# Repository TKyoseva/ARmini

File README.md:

# parts-bot

Written by `.github/workflows/parts.yml`. Do not edit; edit `parts/needs.yaml` on `dev`.

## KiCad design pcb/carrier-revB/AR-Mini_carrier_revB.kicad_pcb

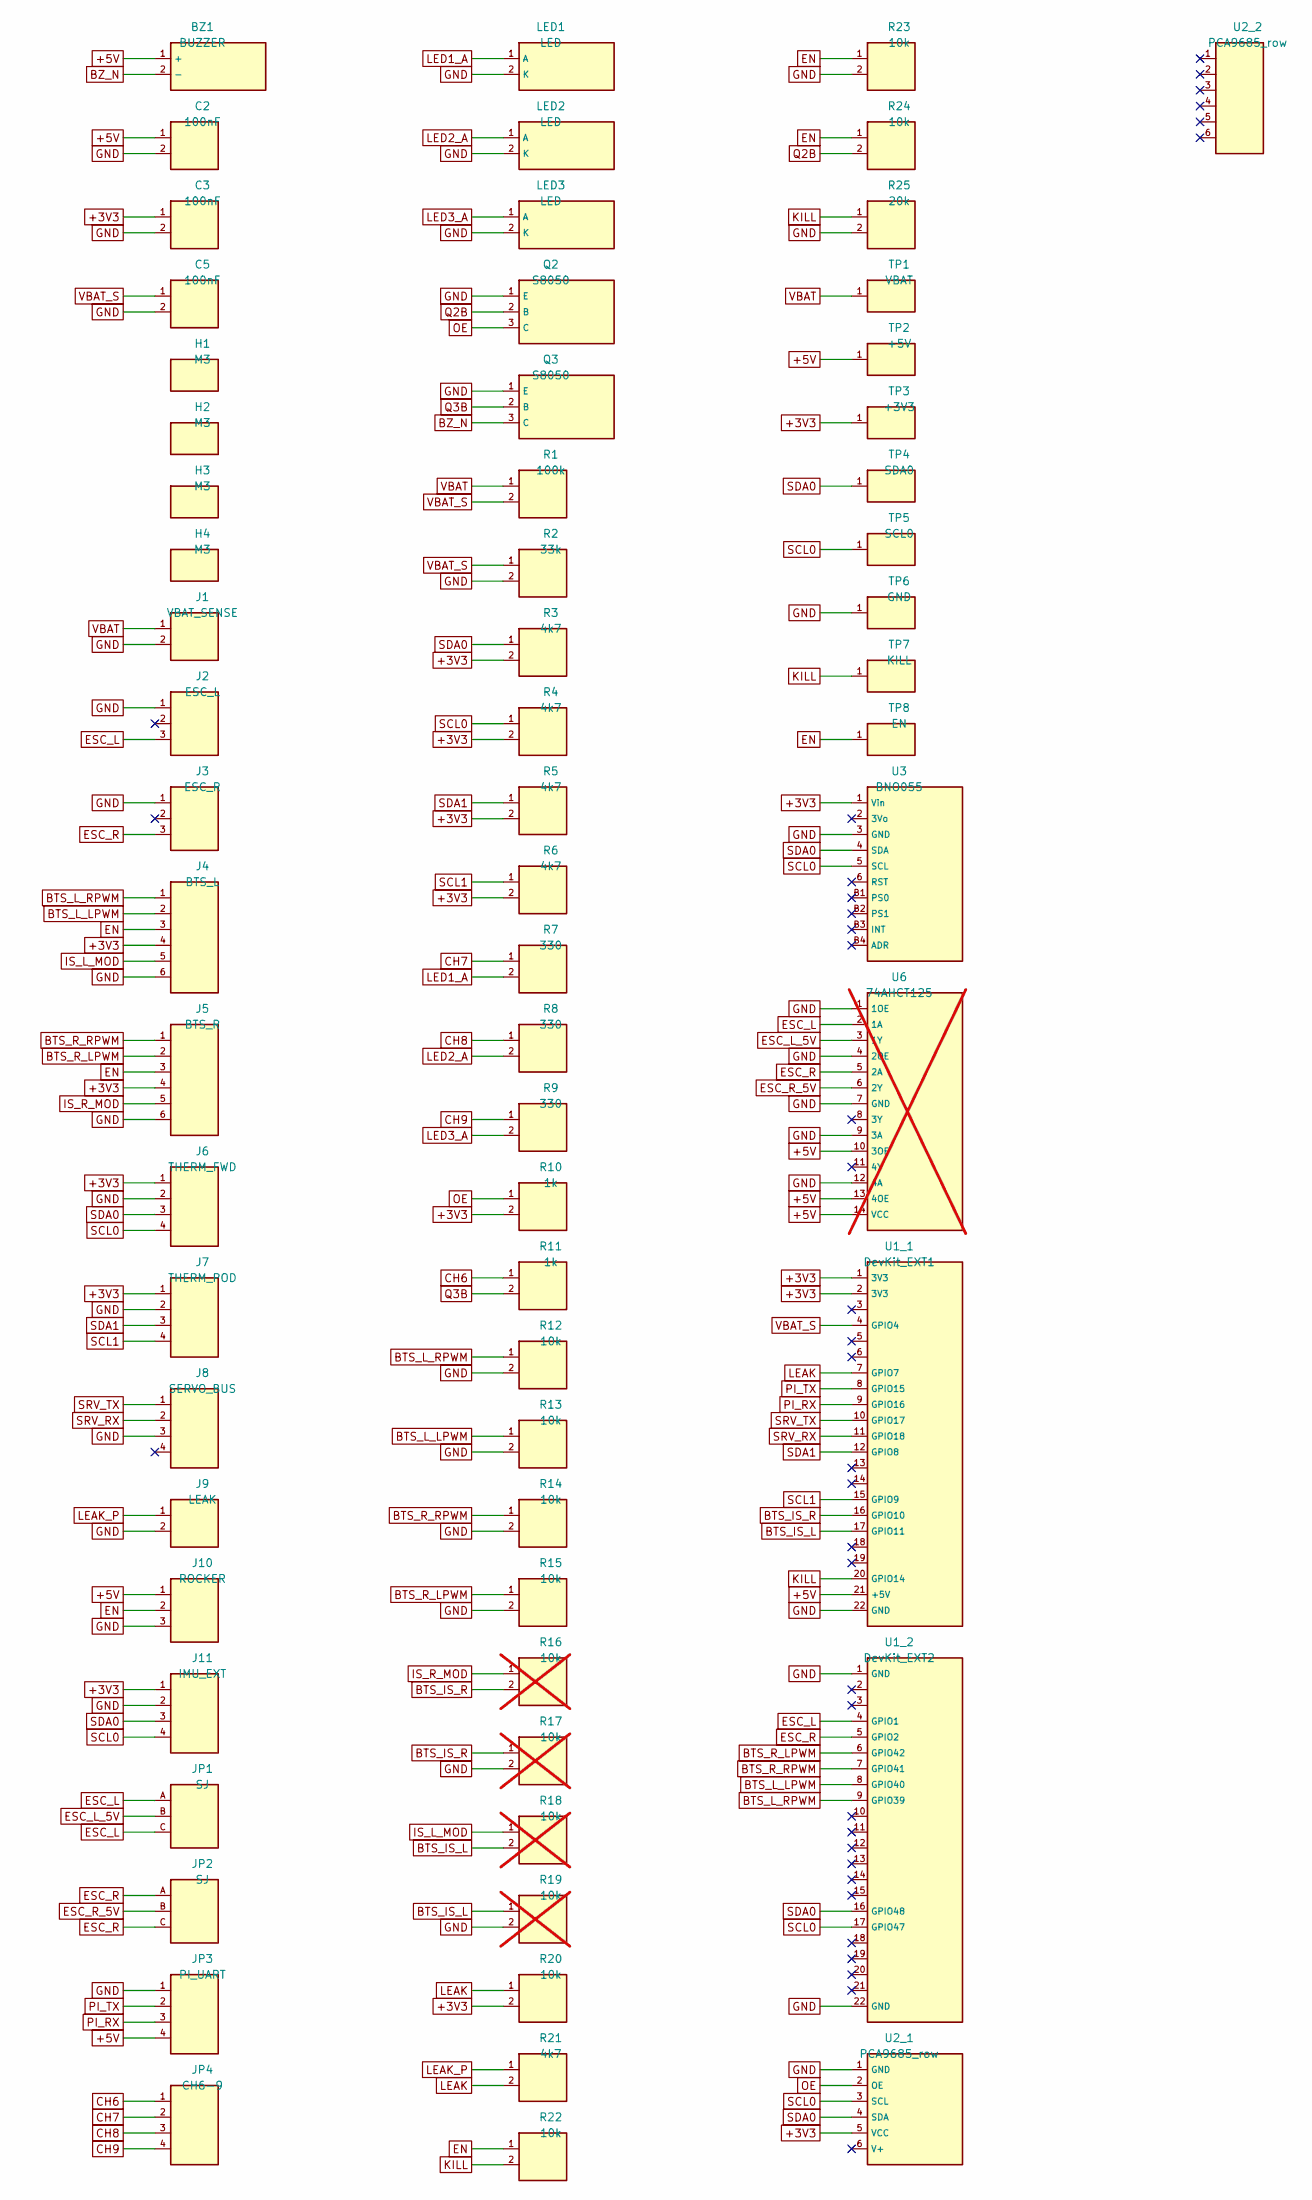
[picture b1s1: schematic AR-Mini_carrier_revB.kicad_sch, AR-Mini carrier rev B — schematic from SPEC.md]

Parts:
BZ1: BUZZER; BZ1
C2: 100nF; C2
C3: 100nF; C3
C5: 100nF; C5
H1, H2, H3, H4: M3
J1: VBAT_SENSE; J1
J2: ESC_L; J2
J3: ESC_R; J3
J4: BTS_L; J4
J5: BTS_R; J5
J6: THERM_FWD; J6
J7: THERM_POD; J7
J8: SERVO_BUS; J8
J9: LEAK; J9
J10: ROCKER; J10
J11: IMU_EXT; J11
JP1: SJ; JP1
JP2: SJ; JP2
JP3: PI_UART; JP3
JP4: CH6-9; JP4
LED1: LED; LED1
LED2: LED; LED2
LED3: LED; LED3
Q2: S8050; Q2
Q3: S8050; Q3
R1: 100k; R1
R2: 33k; R2
R3: 4k7; R3
R4: 4k7; R4
R5: 4k7; R5
R6: 4k7; R6
R7: 330; R7
R8: 330; R8
R9: 330; R9
R10: 1k; R10
R11: 1k; R11
R12: 10k; R12
R13: 10k; R13
R14: 10k; R14
R15: 10k; R15
R16: 10k; R16; not fitted
R17: 10k; R17; not fitted
R18: 10k; R18; not fitted
R19: 10k; R19; not fitted
R20: 10k; R20
R21: 4k7; R21
R22: 10k; R22
R23: 10k; R23
R24: 10k; R24
R25: 20k; R25
TP1: VBAT; TP1
TP2: +5V; TP2
TP3: +3V3; TP3
TP4: SDA0; TP4
TP5: SCL0; TP5
TP6: GND; TP6
TP7: KILL; TP7
TP8: EN; TP8
U1_1: DevKit_EXT1; U1_1
U1_2: DevKit_EXT2; U1_2
U2_1: PCA9685_row; U2_1
U2_2: PCA9685_row; U2_2
U3: BNO055; U3
U6: 74AHCT125; U6; not fitted

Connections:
+3V3: C3.1, J4.4, J5.4, J6.1, J7.1, J11.1, R3.2, R4.2, R5.2, R6.2, R10.2, R20.2, TP3.1, U1_1.1 (3V3), U1_1.2 (3V3), U2_1.5 (VCC), U3.1 (Vin)
+5V: BZ1.1 (+), C2.1, J10.1, JP3.4, TP2.1, U1_1.21 (+5V), U6.10 (3OE), U6.13 (4OE), U6.14 (VCC)
BTS_IS_L: R18.2, R19.1, U1_1.17 (GPIO11)
BTS_IS_R: R16.2, R17.1, U1_1.16 (GPIO10)
BTS_L_LPWM: J4.2, R13.1, U1_2.8 (GPIO40)
BTS_L_RPWM: J4.1, R12.1, U1_2.9 (GPIO39)
BTS_R_LPWM: J5.2, R15.1, U1_2.6 (GPIO42)
BTS_R_RPWM: J5.1, R14.1, U1_2.7 (GPIO41)
BZ_N: BZ1.2 (-), Q3.3 (C)
CH6: JP4.1, R11.1
CH7: JP4.2, R7.1
CH8: JP4.3, R8.1
CH9: JP4.4, R9.1
EN: J4.3, J5.3, J10.2, R22.1, R23.1, R24.1, TP8.1
ESC_L: J2.3, JP1.A, JP1.C, U1_2.4 (GPIO1), U6.2 (1A)
ESC_L_5V: JP1.B, U6.3 (1Y)
ESC_R: J3.3, JP2.A, JP2.C, U1_2.5 (GPIO2), U6.5 (2A)
ESC_R_5V: JP2.B, U6.6 (2Y)
GND: C2.2, C3.2, C5.2, J1.2, J2.1, J3.1, J4.6, J5.6, J6.2, J7.2, J8.3, J9.2, J10.3, J11.2, JP3.1, LED1.2 (K), LED2.2 (K), LED3.2 (K), Q2.1 (E), Q3.1 (E), R2.2, R12.2, R13.2, R14.2, R15.2, R17.2, R19.2, R23.2, R25.2, TP6.1, U1_1.22 (GND), U1_2.1 (GND), U1_2.22 (GND), U2_1.1 (GND), U3.3 (GND), U6.1 (1OE), U6.4 (2OE), U6.7 (GND), U6.9 (3A), U6.12 (4A)
IS_L_MOD: J4.5, R18.1
IS_R_MOD: J5.5, R16.1
KILL: R22.2, R25.1, TP7.1, U1_1.20 (GPIO14)
LEAK: R20.1, R21.2, U1_1.7 (GPIO7)
LEAK_P: J9.1, R21.1
LED1_A: LED1.1 (A), R7.2
LED2_A: LED2.1 (A), R8.2
LED3_A: LED3.1 (A), R9.2
OE: Q2.3 (C), R10.1, U2_1.2 (OE)
PI_RX: JP3.3, U1_1.9 (GPIO16)
PI_TX: JP3.2, U1_1.8 (GPIO15)
Q2B: Q2.2 (B), R24.2
Q3B: Q3.2 (B), R11.2
SCL0: J6.4, J11.4, R4.1, TP5.1, U1_2.17 (GPIO47), U2_1.3 (SCL), U3.5 (SCL)
SCL1: J7.4, R6.1, U1_1.15 (GPIO9)
SDA0: J6.3, J11.3, R3.1, TP4.1, U1_2.16 (GPIO48), U2_1.4 (SDA), U3.4 (SDA)
SDA1: J7.3, R5.1, U1_1.12 (GPIO8)
SRV_RX: J8.2, U1_1.11 (GPIO18)
SRV_TX: J8.1, U1_1.10 (GPIO17)
VBAT: J1.1, R1.1, TP1.1
VBAT_S: C5.1, R1.2, R2.1, U1_1.4 (GPIO4)

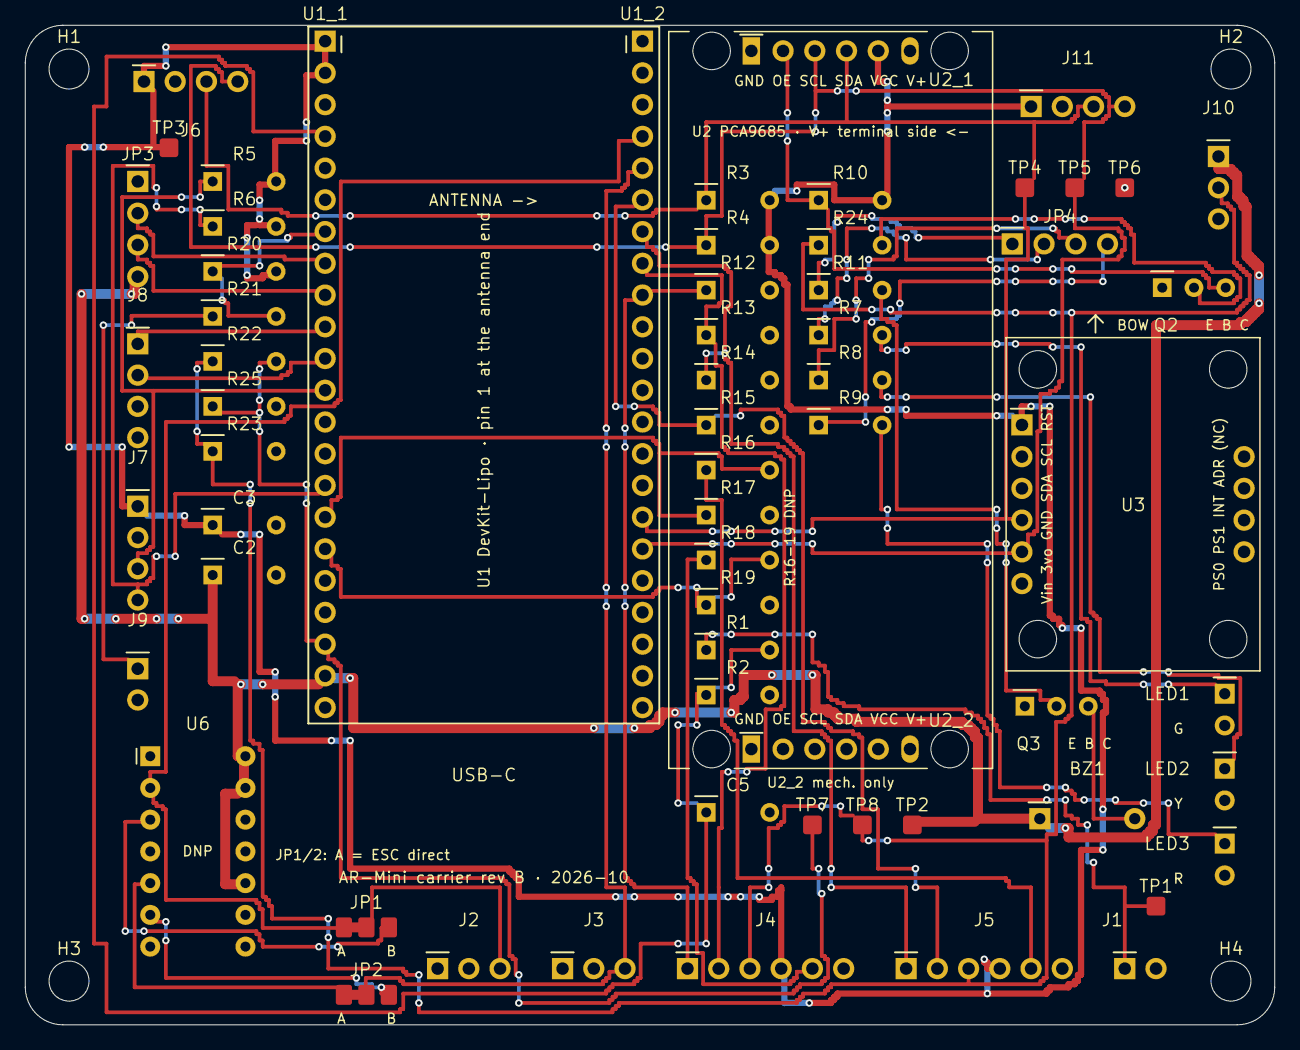
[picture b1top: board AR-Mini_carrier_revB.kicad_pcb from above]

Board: 2 copper layers, 100.0 x 80.0 mm, 67 parts (0 on the bottom side), 40 nets.

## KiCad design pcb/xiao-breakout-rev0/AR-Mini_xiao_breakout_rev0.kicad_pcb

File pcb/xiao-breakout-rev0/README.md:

# AR-Mini XIAO breakout — rev 0 (learning board for Aisler)

50 × 40 mm, 2 layers, THT only. Goal: go the whole way KiCad → DRC → Aisler → soldering → it works, with something that is really used afterwards: this is the XIAO part of the carrier board (sensors, servo bus, 5 V input, battery).

## What is on it
- J1/J2 — 2 × 1×7 female headers for the XIAO ESP32S3 Sense (15.24 mm between the rows). The XIAO's USB-C faces the top edge (silkscreen "USB-C ^").
- J3 I2C0 (JST-XH 4): 3V3 · GND · SDA0 (D4/GPIO5) · SCL0 (D5/GPIO6) → MLX90642-D45, BNO055, PCA9685
- J4 I2C1 (JST-XH 4): **SCL1 (D2/GPIO3) · SDA1 (D3/GPIO4)** · GND · 3V3 → MLX90640-110°. The pin order differs from J3 — on purpose, see the note.
- J5 SERVO (JST-XH 4): RX (D7/GPIO44 ← driver TX) · TX (D6/GPIO43 → driver RX) · GND · NC
- J6 PWR (JST-XH 2): +5 V · GND — from the buck
- J7 VBAT (JST-XH 2): VBAT · GND — from the "5 A logic" fuse (measurement only, almost zero current)
- R1 100k / R2 33k — divider to A0 (D0/GPIO1): 12.6 V → 3.13 V
- R7 330 Ω + LED1 — 3V3 indicator (on = the XIAO is alive)
- H1–H4 — Ø3.2 mounting holes, grid 44 × 34
- GND — pour on the bottom layer; 3V3 and I2C-1 are routed on the bottom, everything else on top.

Note: `Wire1.begin(4, 3)` (SDA=GPIO4, SCL=GPIO3). They are swapped so the tracks do not cross; the carrier board is the same.

## How to open and check it (10 minutes)
1. KiCad 8 or 9 → **PCB Editor** (standalone, without a project) → File → Open → `AR-Mini_xiao_breakout_rev0.kicad_pcb`. The file is in KiCad 7 format; on Save it will be converted — that is normal.
2. Press **B** (Fill all zones) — the bottom layer fills with ground.
3. **Inspect → Design Rules Checker → Run DRC.** Expect 0 errors. Warnings like "footprint not found in library" / "no schematic" are normal for a standalone board — ignore them.
4. **View → 3D Viewer** (Alt+3) — look at it. The headers and JSTs will have no 3D models (generated footprints), only pads — that is fine.
5. To change it before ordering: move tracks with **M**, add them with **X**; Edit → Edit Text and Graphics for the labels.

## Ordering from Aisler (5 minutes)
- Simplest: **aisler.net → New project → Upload** → upload the `.kicad_pcb` directly (they accept KiCad files; no Gerbers needed).
- Or: Plugin and Content Manager → install "AISLER Push for KiCad" → toolbar button → opens the site with the board uploaded.
- Choose: 2 Layer · 1.6 mm · **3 pcs** (minimum) · lead-free HASL (or "Beautiful Boards" for a black mask, +~10 €) · delivery to Bulgaria.
- Expected price: ~15–20 € for three. Lead time: 3–5 working days production + DHL.
- Before "Order": print 1:1 on paper (File → Plot → PDF, scale 1:1) and put the XIAO and the JSTs on the sheet. Every pin in its hole.

## Parts to solder (all THT, 15 minutes with the HS-03)
| What | Qty | From |
|---|---|---|
| Female header 1×7, 2.54 | 2 | Freenove/Joy-IT kit or Ardboard |
| JST-XH 2.5 mm vertical PCB header, 4 pins | 3 | Vikiwat / Ardboard (~0.20 €) |
| JST-XH vertical, 2 pins | 2 | same |
| Resistors 100k, 33k, 330 Ω (1/4 W) | 1 each | the Freenove kit has 330; 100k/33k from Vikiwat |
| LED 5 mm | 1 | the kit |
| M3 × 6 mm standoffs + screws | 4 | ruthex / DSM set |

Soldering order: resistors → LED → JSTs → headers last (with the XIAO plugged in, so they stay parallel).

## What it teaches that goes into the carrier rev A
- whether the 15.24 mm headers fit this XIAO (measured 15.35);
- whether JST-XH pads with a Ø1.0 hole are comfortable for the crimped wires from the Preciva kit;
- how accurate a 1:1 print is on the paper printer;
- how long it really takes from "Order" to "on the desk" with Aisler for Bulgaria — that number is needed for the rev A schedule.

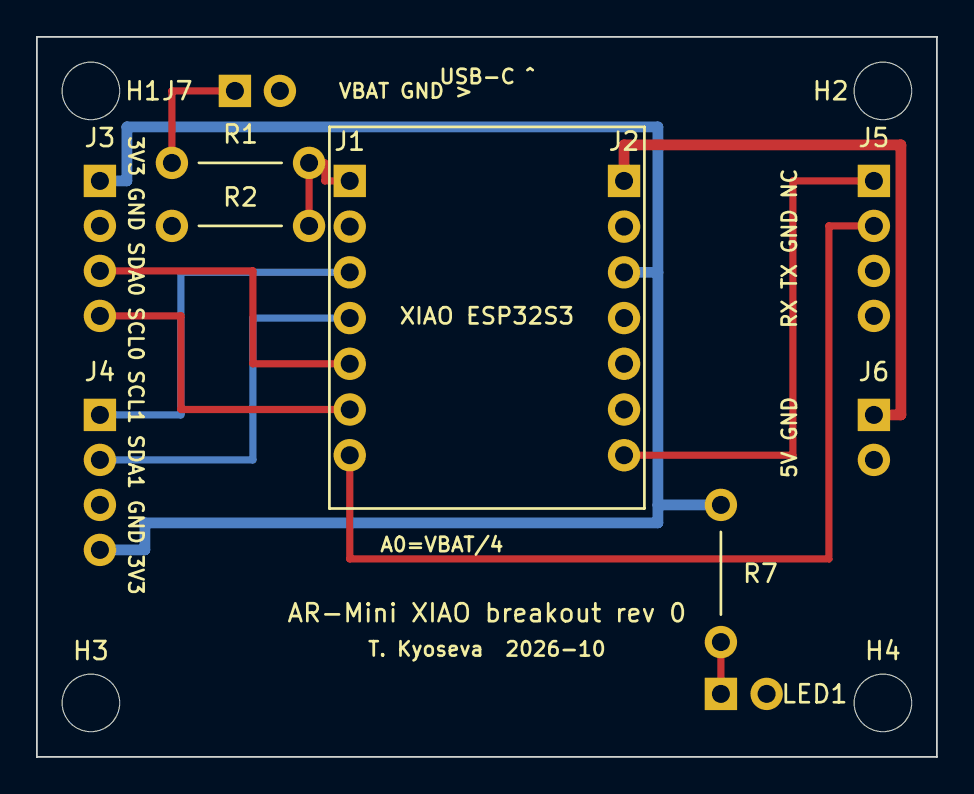
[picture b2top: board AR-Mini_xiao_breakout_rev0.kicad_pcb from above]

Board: 2 copper layers, 50.0 x 40.0 mm, 15 parts (0 on the bottom side), 12 nets.

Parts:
H1, H2, H3, H4: M3
J1: XIAO_L
J2: XIAO_R
J3: I2C0
J4: I2C1
J5: SERVO
J6: PWR5V
J7: VBAT
LED1: PWR
R1: 100k
R2: 33k
R7: 330

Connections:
+3V3: J2.3, J3.1, J4.4, R7.1
+5V: J2.1, J6.1
GND: J2.2, J3.2, J4.3, J5.3, J6.2, J7.2, LED1.2, R2.1
LED_A: LED1.1, R7.2
SCL0: J1.6, J3.4
SCL1: J1.3, J4.1
SDA0: J1.5, J3.3
SDA1: J1.4, J4.2
SRV_RX: J2.7, J5.1
SRV_TX: J1.7, J5.2
VBAT: J7.1, R1.1
VBAT_S: J1.1, R1.2, R2.2

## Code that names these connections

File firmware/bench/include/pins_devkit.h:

// AR-Mini bench · Olimex ESP32-S3-DevKit-Lipo · the ONE place for GPIO numbers.
//
// SOURCE: hardware/breadboard/AR-Mini_breadboard_2b_devkit-lipo.png, table "AR-Mini pins on the DevKit-Lipo"
//         (sheet 2b, T. Kyoseva, 07.10.2026) and hardware/breadboard/Olimex_DevKit-Lipo_pinout_manual-p7.png
//         (Olimex ESP32-S3-DevKit-Lipo user manual rev 2.0, p7, EXT1/EXT2 = DevKitC-1 compatible).
// Every `// VERIFY` below is also listed at the bottom of hardware/wiring/PINOUT.md and in firmware/bench/README.md.
#pragma once

// ---------------------------------------------------------------- I2C-0 (Wire): D45, BNO055, PCA9685 (= pUEXT pins)
#define PIN_I2C0_SDA 48 // SOURCE: breadboard 2b (I²C-0 SDA GPIO48; also pUEXT / manual p7 "GPIO48\I2C_SDA")
#define PIN_I2C0_SCL 47 // SOURCE: breadboard 2b (I²C-0 SCL GPIO47; also pUEXT / manual p7 "GPIO47\I2C_SCL")

// ---------------------------------------------------------------- I2C-1 (Wire1): MLX90640 110°
#define PIN_I2C1_SDA 8 // SOURCE: breadboard 2b (I²C-1 SDA GPIO8, EXT1 row a)
#define PIN_I2C1_SCL 9 // SOURCE: breadboard 2b (I²C-1 SCL GPIO9, EXT1 row a)

// ---------------------------------------------------------------- UART1: Waveshare bus servo adapter
#define PIN_SRV_TX 17 // SOURCE: breadboard 2b (UART1 TX GPIO17 = U1TXD → adapter RX)
#define PIN_SRV_RX 18 // SOURCE: breadboard 2b (UART1 RX GPIO18 = U1RXD ← adapter TX)

// ---------------------------------------------------------------- UART2 (v2): Raspberry Pi 5 — not used on the bench
#define PIN_PI_TX 15 // SOURCE: breadboard 2b (UART2 TX GPIO15)
#define PIN_PI_RX 16 // SOURCE: breadboard 2b (UART2 RX GPIO16)

// ---------------------------------------------------------------- ESC L / R (LEDC 50 Hz) — bench env `esc` (C024)
#define PIN_ESC_L 1 // SOURCE: breadboard 2b (ESC L GPIO1)
#define PIN_ESC_R 2 // SOURCE: breadboard 2b (ESC R GPIO2)

// ---------------------------------------------------------------- BTS7960 L / R
// Sheet 2b gives the pairs "GPIO39/40 · GPIO41/42" but not which one of a pair is RPWM.
// Chosen here: the lower number is RPWM. If the motor runs the wrong way, swap the two wires, not the code.
// GPIO39-42 each have a 10 k pull-down to GND (C015, 11.10): GPIO39 is weakly HIGH after boot and 39/40 in download mode.
// setup() must drive all four LOW before anything else. The rocker (R_EN/L_EN) stays the hardware stop.
#define PIN_BTS_L_RPWM 39 // VERIFY: sheet 2b "BTS7960 L GPIO39/40" — RPWM/LPWM order chosen, not on the sheet
#define PIN_BTS_L_LPWM 40 // VERIFY: see PIN_BTS_L_RPWM
#define PIN_BTS_R_RPWM 41 // VERIFY: sheet 2b "BTS7960 R GPIO41/42" — order chosen, not on the sheet
#define PIN_BTS_R_LPWM 42 // VERIFY: see PIN_BTS_R_RPWM
// BTS7960 current sense (IS_R, IS_L) is NOT on sheet 2b. Two free analog-capable GPIOs on EXT1 are proposed
// (GPIO10 = ADC1_CH9, GPIO11 = ADC2_CH0; both are SPI pins on the manual, unused here; no WiFi so ADC2 is usable).
// Wiring them is optional — see src/bts7960/PROTOCOL.md (the module's IS pin can exceed 3.3 V in fault mode).
#define PIN_BTS_IS_R 10 // VERIFY: not on sheet 2b; proposed free ADC pin, decide + measure before wiring
#define PIN_BTS_IS_L 11 // VERIFY: not on sheet 2b; proposed free ADC pin, decide + measure before wiring

// ---------------------------------------------------------------- ADC
#define PIN_VBAT_ADC 4 // SOURCE: breadboard 2b (ADC VBAT GPIO4 ← divider from F4). C027 bench, measured 100 k / 30 k.
#define PIN_LEAK 7     // SOURCE: breadboard 2b (ADC LEAK GPIO7 ← 10k to 3V3, 4.7k to the probe → GND)

// ---------------------------------------------------------------- KILL (software kill; the 50 A main switch is the hardware one)
#define PIN_KILL 14 // SOURCE: breadboard 2b (KILL GPIO14, 10k pull-up to 3V3, rocker C → GPIO14, KILL → GND; low = KILL)

// ---------------------------------------------------------------- Used by the board itself — never for modules
#define PIN_ONBOARD_PWR_SENS 5 // SOURCE: manual p7 (GPIO5\PWR_SENS)
#define PIN_ONBOARD_BAT_SENS 6 // SOURCE: manual p7 (GPIO6\BAT_SENS) — the board's own 1S LiPo, not the 3S pack
#define PIN_ONBOARD_LED 38     // SOURCE: manual p7 (GPIO38\LED1), active low (sheet 2b)
#define PIN_ONBOARD_BUTTON 0   // SOURCE: manual p7 (GPIO0\BUT1)
// Do not touch: GPIO35–37 (octal PSRAM), GPIO3/45/46 (strapping), GPIO19/20 (USB D+/D−). SOURCE: breadboard 2b

// ---------------------------------------------------------------- Divider / ladder values (for the ladder sketch)
#define VBAT_DIV_R_TOP_OHM 100000.0f // SOURCE: breadboard 2b + pcb/carrier-revA/SPEC.md (R1 100 k, 1 %)
#define VBAT_DIV_R_BOT_OHM 30000.0f  // SOURCE: C027 bench, measured 30 k
#define VBAT_GAIN 0.965f             // SOURCE: C027 (23.10) fit against the meter: v_bat = 0.965 × v_nominal + 0.57
#define VBAT_OFFSET_V 0.57f          // SOURCE: C027 (23.10), same fit
#define LEAK_PULLUP_OHM 10000.0f     // SOURCE: breadboard 2b (10 k to 3V3)
#define LEAK_SERIES_OHM 4700.0f      // SOURCE: breadboard 2b (4.7 k to the probe)

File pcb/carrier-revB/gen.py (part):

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    e1[20] = "+5V"          # SPEC §2/§3 [13.10]: +5V OUT from the DevKit (buck on its OTG USB-C)
    e1[21] = "GND"
    e2[0] = e2[21] = "GND"
    e2[3] = "ESC_L"          # GPIO1, jumper A bridged to J2
    e2[4] = "ESC_R"
    e2[5] = "BTS_R_LPWM"     # GPIO42, EXT2 pin 6
    e2[6] = "BTS_R_RPWM"     # GPIO41
    e2[7] = "BTS_L_LPWM"     # GPIO40
    e2[8] = "BTS_L_RPWM"     # GPIO39
    e2[15] = "SDA0"
    e2[16] = "SCL0"
    return e1, e2
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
